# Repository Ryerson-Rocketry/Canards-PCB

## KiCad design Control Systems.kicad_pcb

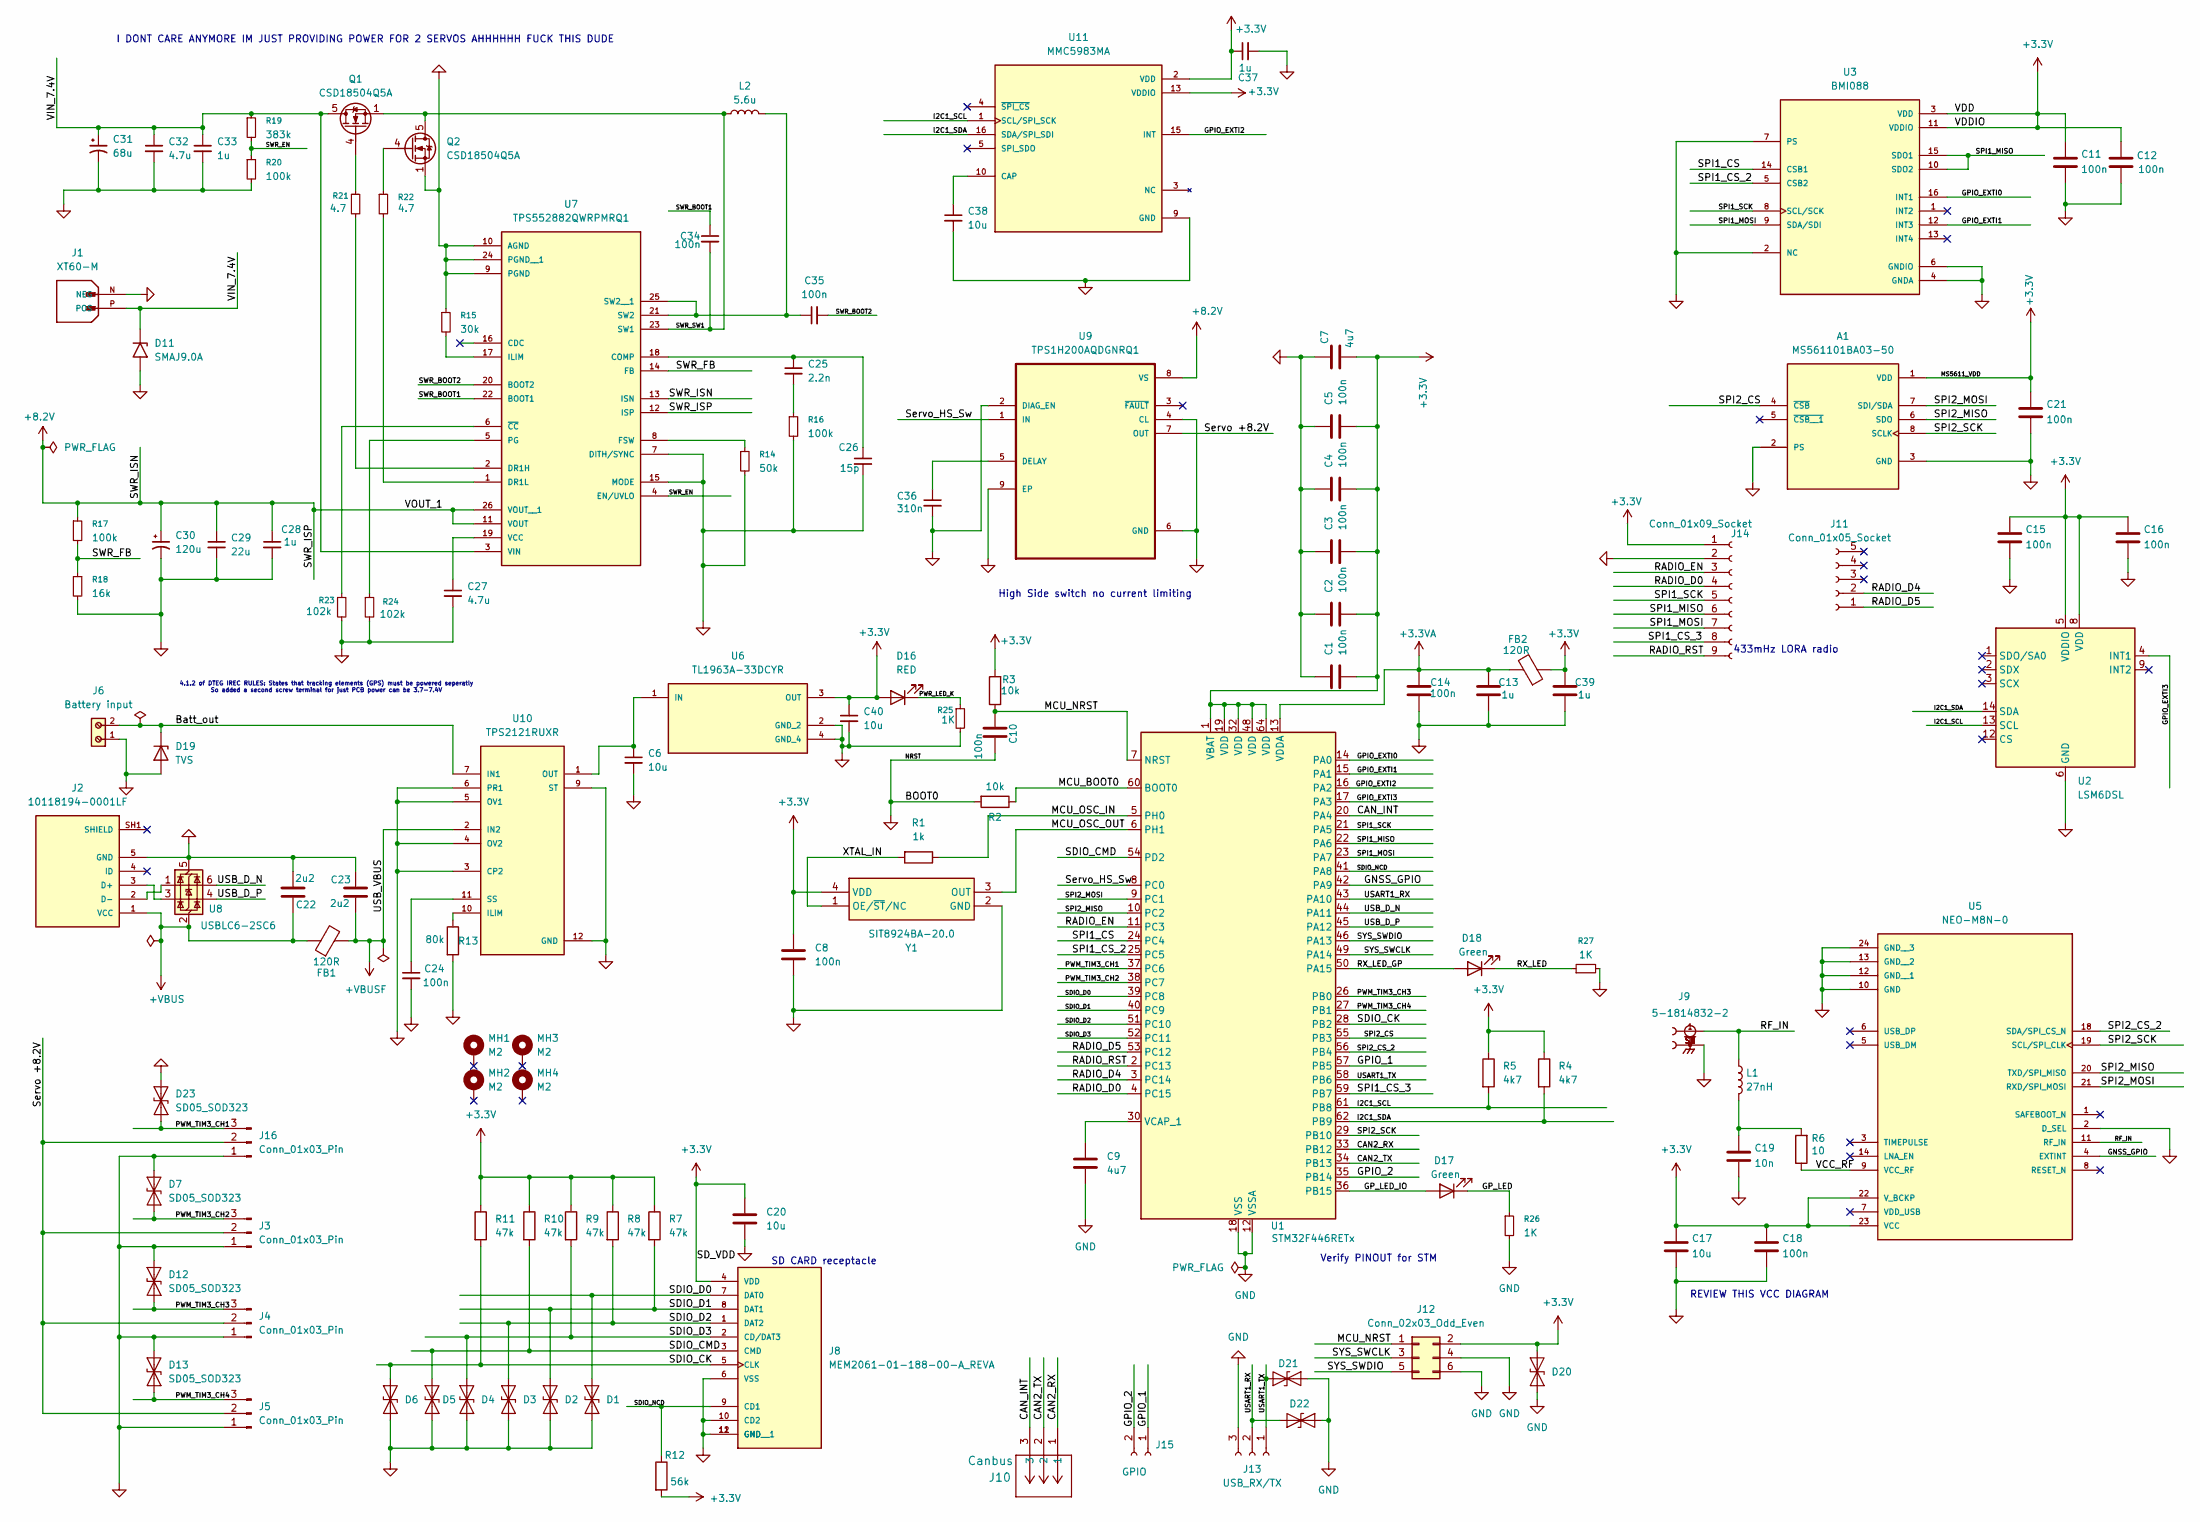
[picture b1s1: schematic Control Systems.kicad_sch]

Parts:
A1: MS561101BA03-50; XDCR_MS561101BA03-50; PARTREV 06/2017
C1, C2, C3, C4, C5, C8, C10, C11, C12, C14, C15, C16, C18, C21, C24, C34, C35: 100n; C_0402_1005Metric
C6, C17, C20, C38, C40: 10u; C_0603_1608Metric
C7, C9: 4u7; C_0402_1005Metric
C13, C28, C33, C37, C39: 1u; C_0402_1005Metric
C19: 10n; C_0402_1005Metric
C22, C23: 2u2; C_0402_1005Metric
C25: 2.2n; C_0402_1005Metric
C26: 15p; C_0402_1005Metric
C27, C32: 4.7u; C_0402_1005Metric
C29: 22u; C_0805_2012Metric
C30: 120u; CP_Elec_6.3x5.9
C31: 68u; CP_Elec_10x12.6
C36: 310n; C_0402_1005Metric
D1, D2, D3, D4, D5, D6, D20, D21, D22: ESD9B3.3ST5G; D_SOD-923
D7, D12, D13, D23: SD05_SOD323; D_SOD-323
D11: SMAJ9.0A; D_SMA
D16: RED; LED_0603_1608Metric
D17, D18: Green; LED_0603_1608Metric
D19: TVS; Nexperia_DSN1608-2_1.6x0.8mm
FB1, FB2: 120R; L_0603_1608Metric
J1: XT60-M; AMASS_XT60-M; PARTREV V1.2
J2: 10118194-0001LF; AMPHENOL_10118194-0001LF; PARTREV D
J3, J4, J5, J16: Conn_01x03_Pin; PinHeader_1x03_P2.54mm_Vertical
J6: Battery input; 691137710002
J8: MEM2061-01-188-00-A_REVA; GCT_MEM2061-01-188-00-A_REVA
J9: 5-1814832-2; SMA_CONN_TE_5-1814832-2; PARTREV C
J10: Canbus; CONN_SD-39357-001_03P_MOL
J11: Conn_01x05_Socket; PinSocket_1x05_P2.54mm_Vertical
J12: Conn_02x03_Odd_Even; PinHeader_2x03_P2.54mm_Vertical
J13: USB_RX/TX; PinSocket_1x03_P2.54mm_Vertical
J14: Conn_01x09_Socket; PinSocket_1x09_P2.54mm_Vertical
J15: GPIO; PinSocket_1x02_P2.54mm_Vertical
L1: 27nH; L_0603_1608Metric
L2: 5.6u; L_0603_1608Metric
MH1, MH2, MH3, MH4: M2; MountingHole_2.2mm_M2_Pad_Via
Q1, Q2: CSD18504Q5A; TDSON-8-1
R1: 1k; R_0402_1005Metric
R2, R3: 10k; R_0402_1005Metric
R4: 4k7; C_0402_1005Metric
R5: 4k7; R_0402_1005Metric
R6: 10; R_0402_1005Metric
R7, R8, R9, R10, R11: 47k; R_0603_1608Metric
R12: 56k; R_0603_1608Metric
R13: 80k; R_0603_1608Metric
R14: 50k; R_0603_1608Metric
R15: 30k; R_0603_1608Metric
R16, R17, R20: 100k; R_0603_1608Metric
R18: 16k; R_0603_1608Metric
R19: 383k; R_0603_1608Metric
R21, R22: 4.7; R_0402_1005Metric
R23, R24: 102k; R_0603_1608Metric
R25, R26, R27: 1K; R_0402_1005Metric
U1: STM32F446RETx; LQFP-64_10x10mm_P0.5mm
U2: LSM6DSL; LGA-14_3x2.5mm_P0.5mm_LayoutBorder3x4y
U3: BMI088
U5: NEO-M8N-0; XCVR_NEO-M8N-0; PARTREV R04
U6: TL1963A-33DCYR; VREG_TL1963A-33DCYR; PARTREV G
U7: TPS552882QWRPMRQ1; CONV_TPS552882QWRPMRQ1; PARTREV A
U8: USBLC6-2SC6; SOT-23-6
U9: TPS1H200AQDGNRQ1; TPS1H200
U10: TPS2121RUXR; IC_TPS2121RUXR; DigiKey_Part_Number 296-53410-1-ND
U11: MMC5983MA; PQFN50P300X300X100-16N; PARTREV A
Y1: SIT8924BA-20.0; QFN_3225_4pins; Manufacturer_Part_Number SIT8924BA-22-33E-20.000000

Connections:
+3.3V: A1.1 (VDD), C1.2, C2.2, C3.2, C4.2, C5.2, C7.2, C8.1, C11.1, C12.1, C15.1, C16.1, C17.1, C18.1, C20.1, C21.1, C37.1, C39.2, C40.1, D16.2 (A), D20.2 (A2), FB2.1, J8.4 (VDD), J12.2, J14.1, R3.2, R4.1, R5.1, R7.1, R8.1, R9.1, R10.1, R11.1, R12.2, U1.1 (VBAT), U1.19 (VDD), U1.32 (VDD), U1.48 (VDD), U1.64 (VDD), U2.5 (VDDIO), U2.8 (VDD), U3.3 (VDD), U3.11 (VDDIO), U5.22 (V_BCKP), U5.23 (VCC), U6.3 (OUT), U11.2 (VDD), U11.13 (VDDIO), Y1.4 (VDD)
+3.3VA: C13.2, C14.2, FB2.2, U1.13 (VDDA)
+8.2V: C28.1, C29.1, C30.1, R17.1, U7.11 (VOUT), U7.12 (ISP), U7.13 (ISN), U7.26 (VOUT__1), U9.8 (VS)
+VBUS: C22.1, FB1.1, J2.1 (VCC), U8.2 (GND)
+VBUSF: C23.1, FB1.2, U10.2 (IN2), U10.2_1 (IN2)
/Batt_out: D19.1 (K), J6.2, U10.7 (IN1), U10.7_1 (IN1)
/CAN2_RX: J10.1, U1.33 (PB12)
/CAN2_TX: J10.2, U1.34 (PB13)
/CAN_INT: J10.3, U1.20 (PA4)
/GNSS_GPIO: U1.42 (PA9), U5.4 (EXTINT)
/GPIO_1: J15.1, U1.57 (PB5)
/GPIO_2: J15.2, U1.35 (PB14)
/GPIO_EXTI0: U1.14 (PA0), U3.16 (INT1)
/GPIO_EXTI1: U1.15 (PA1), U3.12 (INT3)
/GPIO_EXTI2: U1.16 (PA2), U11.15 (INT)
/GPIO_EXTI3: U1.17 (PA3), U2.4 (INT1)
/GP_LED: D17.1 (K), R26.1
/GP_LED_IO: D17.2 (A), U1.36 (PB15)
/I2C1_SCL: R5.2, U1.61 (PB8), U2.13 (SCL), U11.1 (SCL/SPI_SCK)
/I2C1_SDA: R4.2, U1.62 (PB9), U2.14 (SDA), U11.16 (SDA/SPI_SDI)
/MCU_BOOT0: R2.1, U1.60 (BOOT0)
/MCU_NRST: C10.2, J12.1, R3.1, U1.7 (NRST)
/MCU_OSC_IN: R1.1, U1.5 (PH0)
/MCU_OSC_OUT: U1.6 (PH1), Y1.3 (OUT)
/PWM_TIM3_CH1: D23.1 (A1), J16.3, U1.37 (PC6)
/PWM_TIM3_CH2: D7.1 (A1), J3.3, U1.38 (PC7)
/PWM_TIM3_CH3: D12.1 (A1), J4.3, U1.26 (PB0)
/PWM_TIM3_CH4: D13.1 (A1), J5.3, U1.27 (PB1)
/PWR_LED_K: D16.1 (K), R25.1
/RADIO_D0: J14.4, U1.4 (PC15)
/RADIO_D4: J11.2, U1.3 (PC14)
/RADIO_D5: J11.1, U1.53 (PC12)
/RADIO_EN: J14.3, U1.11 (PC3)
/RADIO_RST: J14.9, U1.2 (PC13)
/RF_IN: J9.1, L1.1, U5.11 (RF_IN)
/RX_LED: D18.1 (K), R27.1
/RX_LED_GP: D18.2 (A), U1.50 (PA15)
/SDIO_CK: D6.2 (A2), J8.5 (CLK), R11.2, U1.28 (PB2)
/SDIO_CMD: D5.2 (A2), J8.3 (CMD), R10.2, U1.54 (PD2)
/SDIO_D0: D1.2 (A2), J8.7 (DAT0), U1.39 (PC8)
/SDIO_D1: D2.2 (A2), J8.8 (DAT1), R7.2, U1.40 (PC9)
/SDIO_D2: D3.2 (A2), J8.1 (DAT2), R8.2, U1.51 (PC10)
/SDIO_D3: D4.2 (A2), J8.2 (CD/DAT3), R9.2, U1.52 (PC11)
/SDIO_NCD: J8.9 (CD1), R12.1, U1.41 (PA8)
/SPI1_CS: U1.24 (PC4), U3.14 (CSB1)
/SPI1_CS_2: U1.25 (PC5), U3.5 (CSB2)
/SPI1_CS_3: J14.8, U1.59 (PB7)
/SPI1_MISO: J14.6, U1.22 (PA6), U3.10 (SDO2), U3.15 (SDO1)
/SPI1_MOSI: J14.7, U1.23 (PA7), U3.9 (SDA/SDI)
/SPI1_SCK: J14.5, U1.21 (PA5), U3.8 (SCL/SCK)
/SPI2_CS: A1.4 (~CSB), U1.55 (PB3)
/SPI2_CS_2: U1.56 (PB4), U5.18 (SDA/SPI_CS_N)
/SPI2_MISO: A1.6 (SDO), U1.10 (PC2), U5.20 (TXD/SPI_MISO)
/SPI2_MOSI: A1.7 (SDI/SDA), U1.9 (PC1), U5.21 (RXD/SPI_MOSI)
/SPI2_SCK: A1.8 (SCLK), U1.29 (PB10), U5.19 (SCL/SPI_CLK)
/SWR_BOOT1: C34.1, U7.22 (BOOT1)
/SWR_BOOT2: C35.2, U7.20 (BOOT2)
/SWR_EN: R19.2, R20.1, U7.4 (EN/UVLO)
/SWR_FB: R17.2, R18.1, U7.14 (FB)
/SWR_SW1: C34.2, L2.1, Q1.1 (S), Q1.2 (S), Q1.3 (S), Q2.5 (D), U7.23 (SW1)
/SYS_SWCLK: J12.3, U1.49 (PA14)
/SYS_SWDIO: J12.5, U1.46 (PA13)
/Servo +8.2V: J3.2, J4.2, J5.2, J16.2, U9.7 (OUT)
/Servo_HS_Sw: U1.8 (PC0), U9.1 (IN)
/USART1_RX: D22.2 (A2), J13.2, U1.43 (PA10)
/USART1_TX: D21.2 (A2), J13.1, U1.58 (PB6)
/USB_D_N: U1.44 (PA11), U8.6 (I/O1)
/USB_D_P: U1.45 (PA12), U8.4 (I/O2)
/VCC_RF: R6.1, U5.9 (VCC_RF)
/VIN_7.4V: C31.1, C32.1, C33.1, D11.1 (A1), J1.P (POS), Q1.5 (D), R19.1, U7.3 (VIN)
/XTAL_IN: R1.2, Y1.1 (OE/~ST/NC)
unnamed: C19.1, L1.2, R6.2
unnamed: C25.2, R16.1
unnamed: J2.3 (D+), U8.3 (I/O2)
unnamed: J2.2 (D-), U8.1 (I/O1)
unnamed: Q1.4 (G), R21.1
unnamed: Q2.4 (G), R22.1
unnamed: C9.1, U1.30 (VCAP_1)
unnamed: C6.1, U6.1 (IN), U10.1 (OUT), U10.1_1 (OUT), U10.8 (OUT), U10.8_1 (OUT)
unnamed: C25.1, C26.1, U7.18 (COMP)
unnamed: R21.2, U7.2 (DR1H)
unnamed: R22.2, U7.1 (DR1L)
unnamed: R14.1, U7.8 (FSW)
unnamed: R15.2, U7.17 (ILIM)
unnamed: R24.1, U7.5 (PG)
unnamed: C35.1, L2.2, U7.21 (SW2), U7.25 (SW2__1)
unnamed: C27.1, U7.19 (VCC)
unnamed: R23.1, U7.6 (~CC)
unnamed: C36.1, U9.5 (DELAY)
unnamed: R13.1, U10.10 (ILIM)
unnamed: C24.1, U10.11 (SS)
unnamed: C38.1, U11.10 (CAP)

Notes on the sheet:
SD CARD receptacle
4.1.2 of DTEG IREC RULES: States that tracking elements (GPS) must be powered seperatly So added a second screw terminal for just PCB power can be 3.7-7.4V
High Side switch no current limiting
Verify PINOUT for STM
I DONT CARE ANYMORE IM JUST PROVIDING POWER FOR 2 SERVOS AHHHHHH FUCK THIS DUDE
REVIEW THIS VCC DIAGRAM
433mHz LORA radio

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
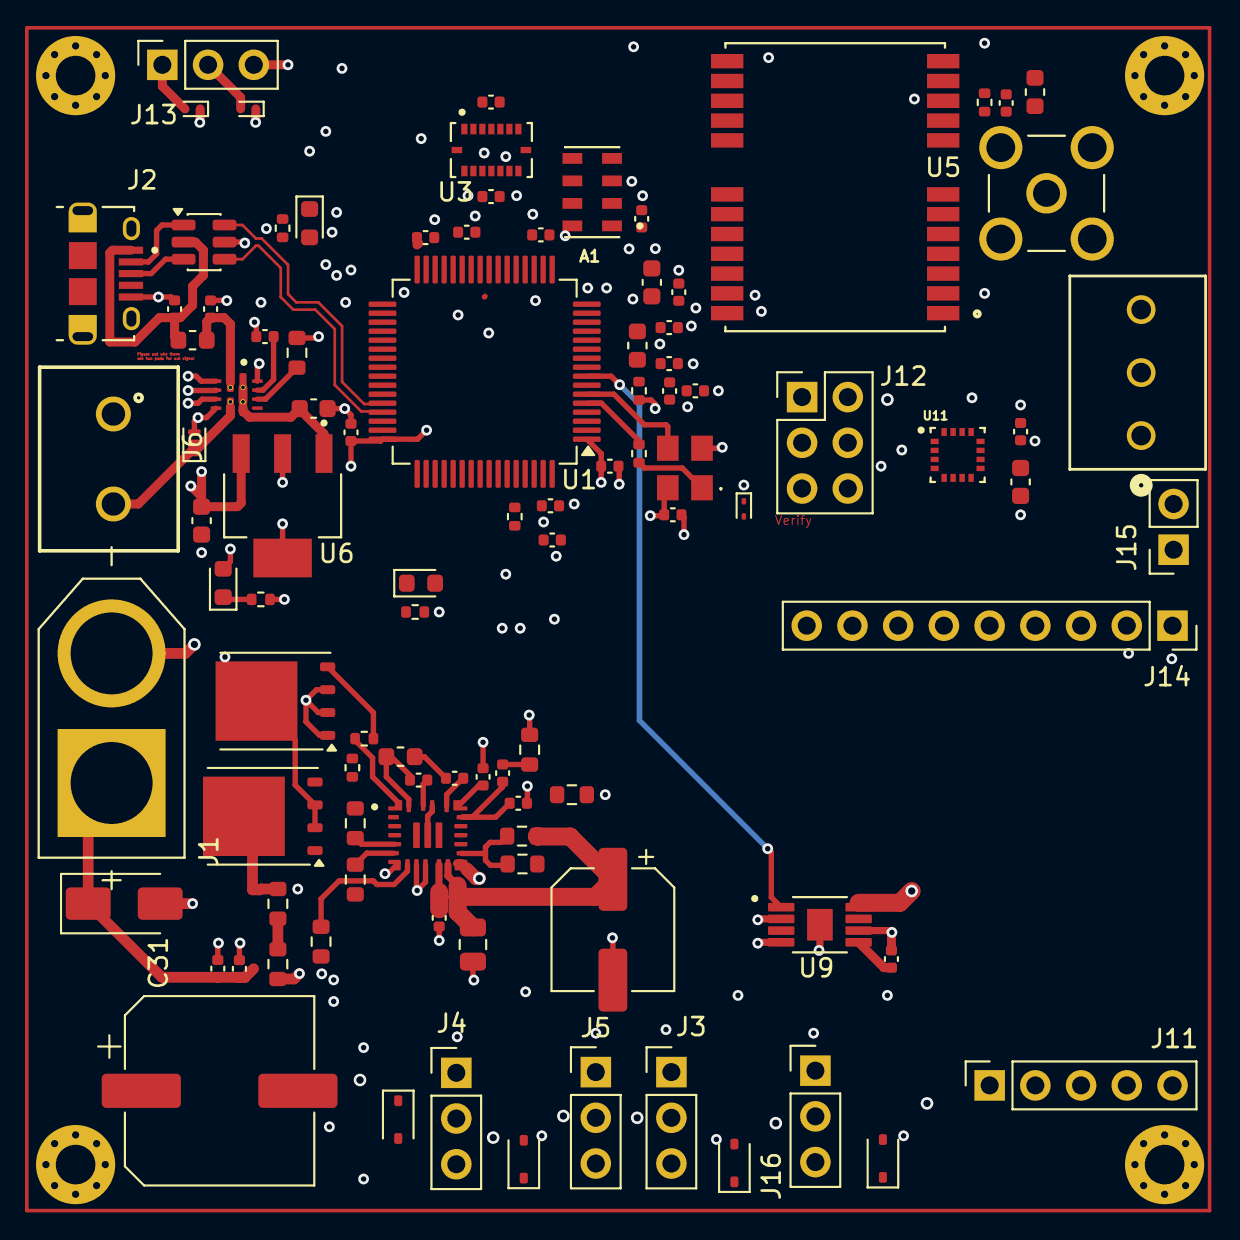
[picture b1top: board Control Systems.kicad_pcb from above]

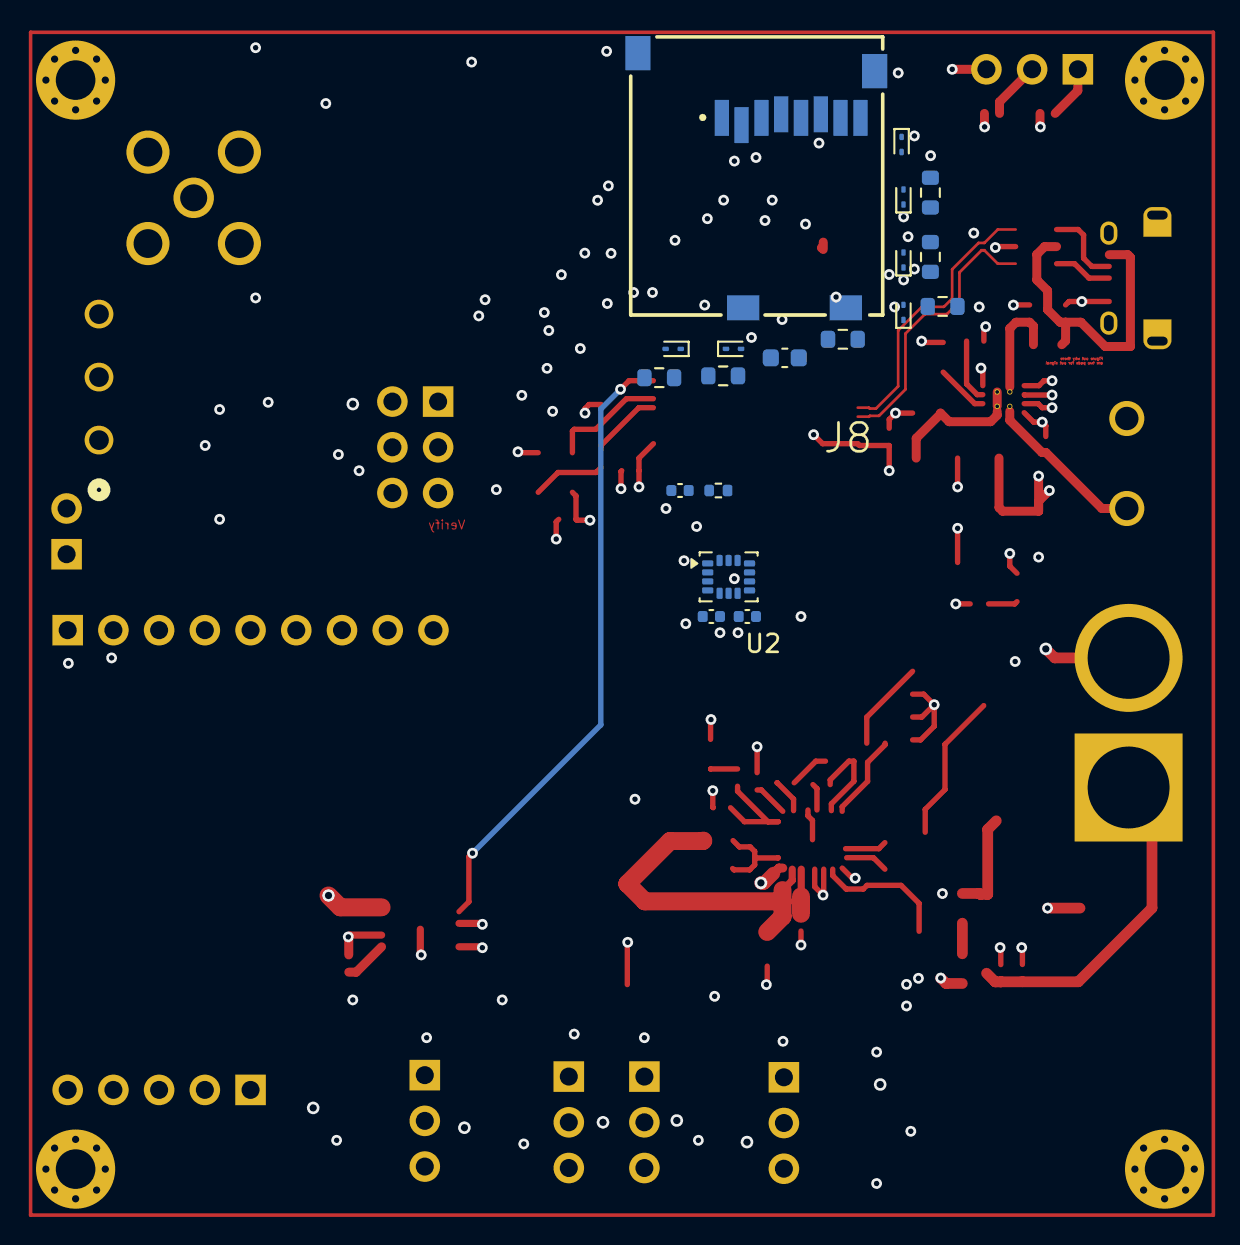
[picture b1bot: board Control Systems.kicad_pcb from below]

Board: 4 copper layers, 122 parts (19 on the bottom side), 93 nets.

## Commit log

2025-10-08 Feat: Added STM32F446RE chip, added Power pins and bootloader
    - Added pins for power supply and GND pins
    - Added switch to bootloader to determine if flash or run code
    - Added Reset pin and added capacitor to prevent spurious reset
2025-10-19 feat: added SWD and SDO and apply pins to connect to ST-LINK pins
2025-10-21 Test branch
2025-11-07 feat: added SWD and SDO and apply pins to connect to ST-LINK pins (#1)
2025-11-10 Added altium schematic DO NOT ADD TO MAIN
2025-11-10 added library folder
2025-11-10 Feat: Added wiring for the MCU for 4 components
    - added almost all passive components
    - added ports for PWM headers
    - wired the main IMU, mag and barometer
2025-11-14 test
2025-11-14 Replace project title with a greeting
2025-11-15 Feat: Wiring done for 3/4 mcu components
    -Left BMI088 alone as it was done
    -Double check the SP2 NSS,
2025-12-14 Finished all sensors, added LDO, and GPS wiring
2025-12-16 Feat: Finished voltage regulator and interupts
2025-12-17 feat: minor changes and updates to schematic
2025-12-17 feat: Final touches
2025-12-17 feat: Final Final touches
2025-12-17 Feat: Minor changes and fixes
2025-12-17 Feat: added USB RX and TX headers
2025-12-17 Feat: Finished ERC, Starting routing
2025-12-18 Feat: PCB footprints and models assigned, basic routing finished
2025-12-22 Placement of components and initial VIA placement
2025-12-23 Feat: VIAs placed and some routing
2026-04-08 Add image to README
2026-06-26 Add new image to README
2026-06-26 Add new image to README (#7)
